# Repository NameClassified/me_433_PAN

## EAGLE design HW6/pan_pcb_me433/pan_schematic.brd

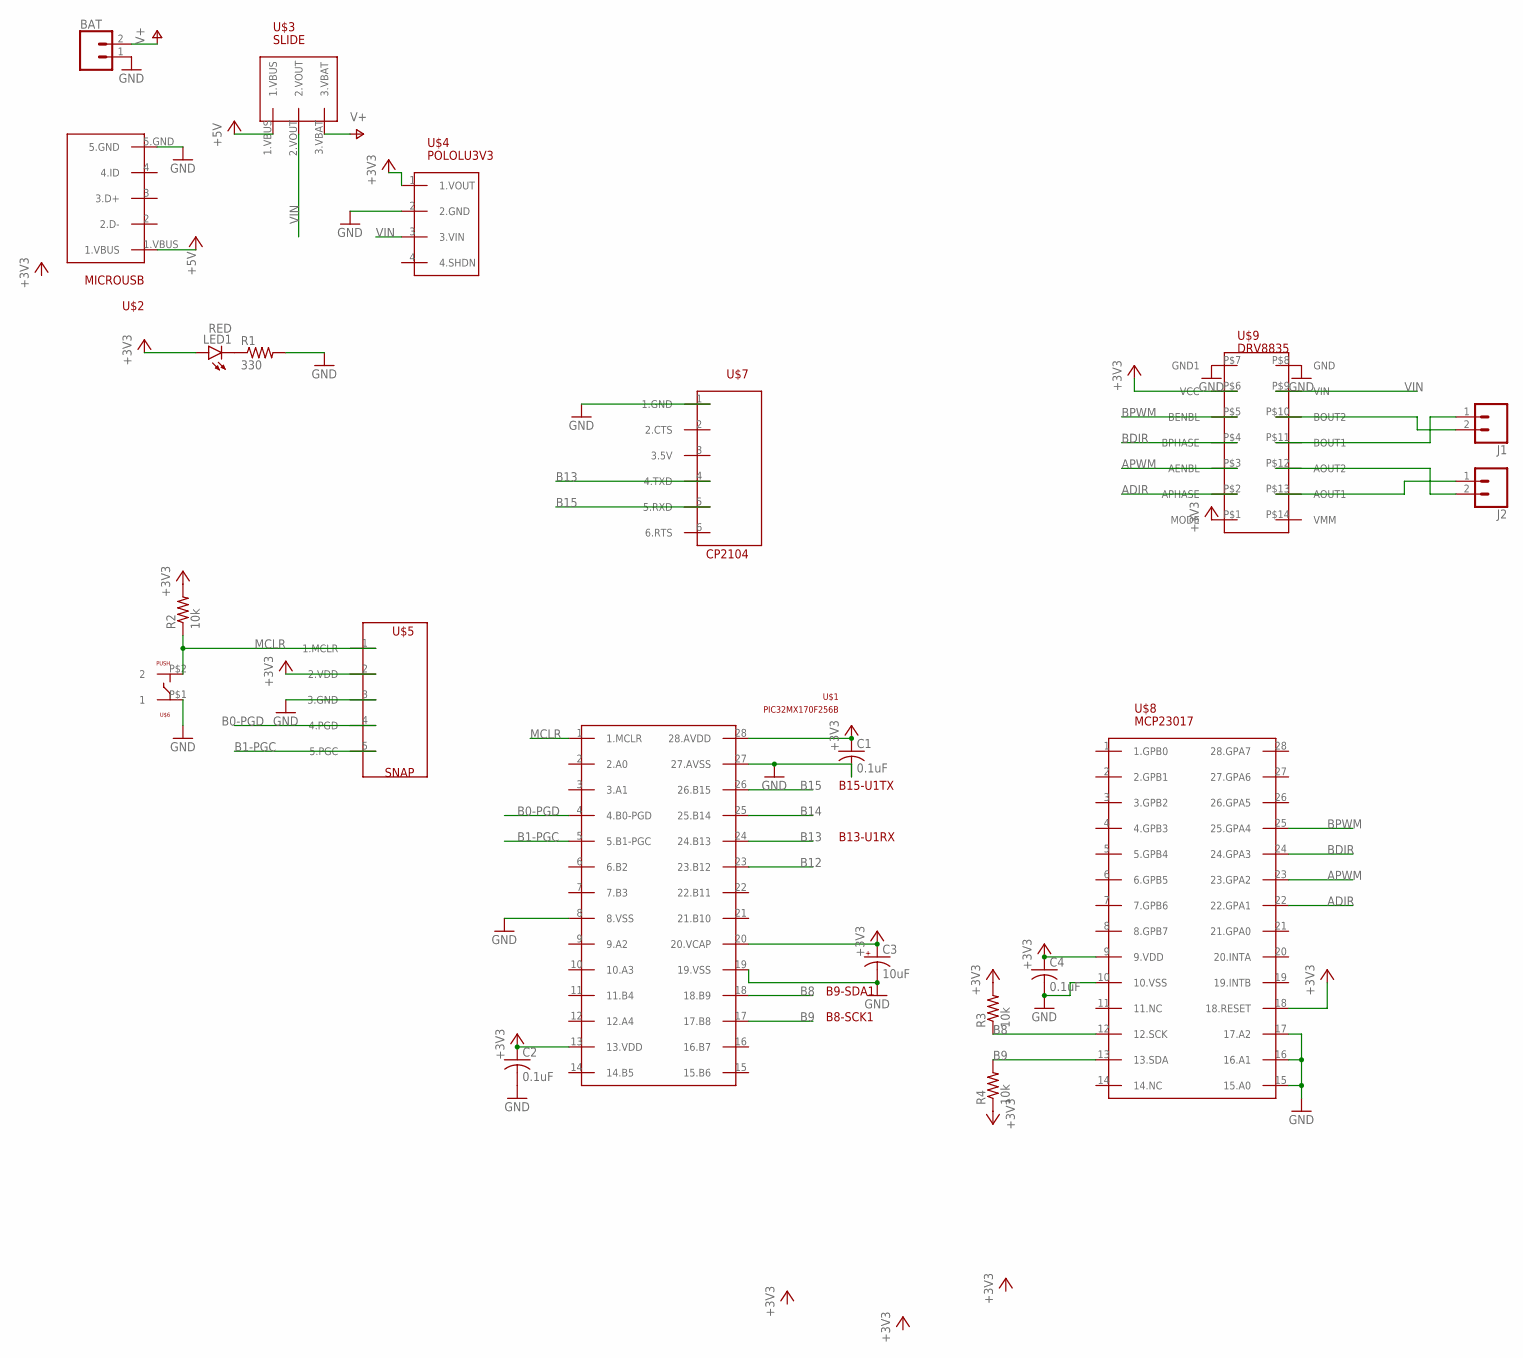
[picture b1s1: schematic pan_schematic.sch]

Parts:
BAT: CONN_02; 1X02
C1, C2, C4: 0.1uF; C025-030X050
C3: 10uF; B45181B
J1, J2: CONN_02POLAR; MOLEX-1X2
LED1: RED; LED3MM
R1: 330; 0207/10
R2: 10k; 0207/10
R3, R4: 10k; M2012
U$1: PIC32MX170F256B; DIL28-3
U$2: MICROUSB
U$3: SLIDE
U$4: POLOLU3V3
U$5: SNAP; 1X05_1.27MM
U$6: PUSH
U$7: CP2104; 1X06
U$8: MCP23017
U$9: DRV8835

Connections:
+3V3: C1.1, C2.1, C3.+, C4.1, LED1.A, R2.2, R3.2, R4.1, U$1.13 (13.VDD), U$1.20 (20.VCAP), U$1.28 (28.AVDD), U$4.1 (1.VOUT), U$5.2 (2.VDD), U$8.9 (9.VDD), U$8.18 (18.RESET), U$9.P$6 (VCC)
+5V: U$2.1.VBUS, U$3.1.VBUS
ADIR: U$8.22 (22.GPA1), U$9.P$2 (APHASE)
APWM: U$8.23 (23.GPA2), U$9.P$3 (AENBL)
B0-PGD: U$1.4 (4.B0-PGD), U$5.4 (4.PGD)
B1-PGC: U$1.5 (5.B1-PGC), U$5.5 (5.PGC)
B8: R3.1, U$1.18 (18.B9), U$8.12 (12.SCK)
B9: R4.2, U$1.17 (17.B8), U$8.13 (13.SDA)
B12: U$1.23 (23.B12)
B13: U$1.24 (24.B13), U$7.4 (4.TXD)
B14: U$1.25 (25.B14)
B15: U$1.26 (26.B15), U$7.5 (5.RXD)
BDIR: U$8.24 (24.GPA3), U$9.P$4 (BPHASE)
BPWM: U$8.25 (25.GPA4), U$9.P$5 (BENBL)
GND: BAT.1, C1.2, C2.2, C3.-, C4.2, R1.2, U$1.8 (8.VSS), U$1.19 (19.VSS), U$1.27 (27.AVSS), U$2.5.GND, U$4.2 (2.GND), U$5.3 (3.GND), U$6.P$1 (1), U$7.1 (1.GND), U$8.10 (10.VSS), U$8.15 (15.A0), U$8.16 (16.A1), U$8.17 (17.A2)
MCLR: R2.1, U$1.1 (1.MCLR), U$5.1 (1.MCLR), U$6.P$2 (2)
unnamed: LED1.K (C), R1.1
unnamed: J1.1, U$9.P$11 (BOUT1)
unnamed: J1.2, U$9.P$10 (BOUT2)
unnamed: J2.2, U$9.P$12 (AOUT2)
unnamed: J2.1, U$9.P$13 (AOUT1)
V+: BAT.2, U$3.3.VBAT
VIN: U$3.2.VOUT, U$4.3 (3.VIN), U$9.P$9 (VIN)

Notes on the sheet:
B15-U1TX
B13-U1RX
B9-SDA1
B8-SCK1

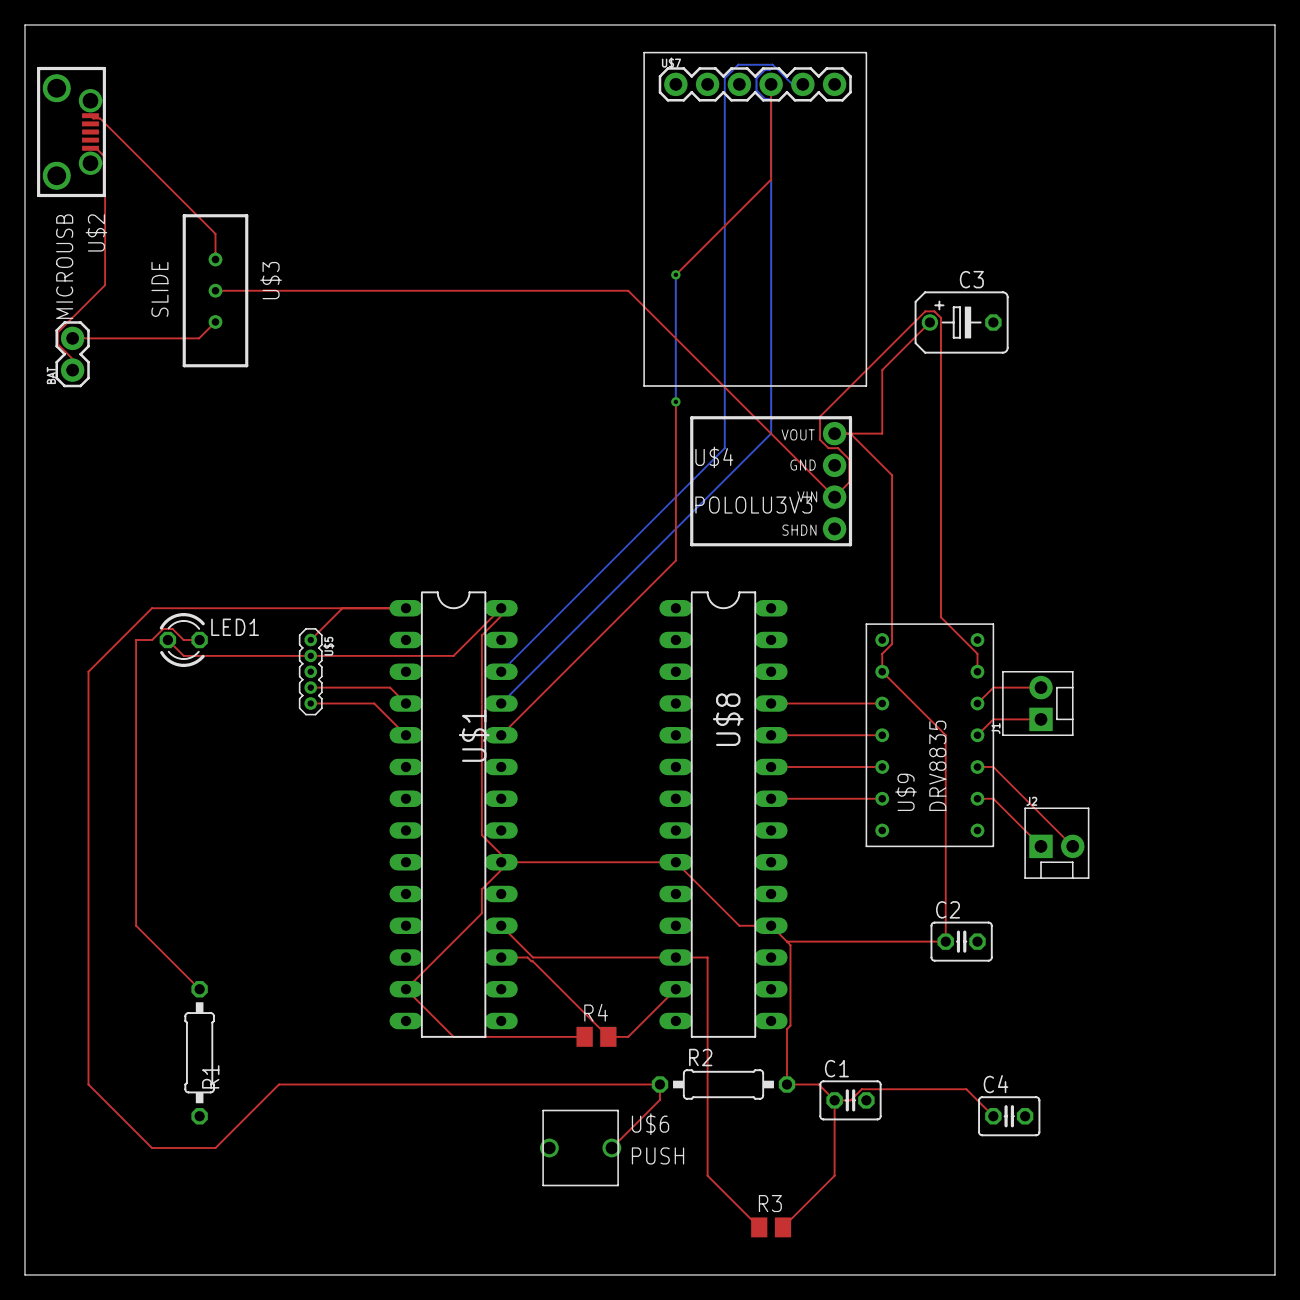
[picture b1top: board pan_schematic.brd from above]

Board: 2 copper layers, 100.0 x 100.0 mm, 21 parts (0 on the bottom side), 21 nets.

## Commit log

2021-05-11 added HW2
2021-05-11 actual progress on HW2
2021-05-11 IIR done
    IIR done
2021-05-11 done
    added FIR
2021-05-28 HW4 done
2021-06-01 HW5 done
2021-06-01 added HW5 demo vid
2021-06-23 HW16 done
2021-06-28 HW15 done-ish
2021-08-30 HW7 done (finally)
2021-09-14 HW8 DONE
    hw8 done
2021-11-22 HW6 done
